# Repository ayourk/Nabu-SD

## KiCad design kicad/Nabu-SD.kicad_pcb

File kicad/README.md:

# SD Card Expansion & More!

Original design by Ken "The Codeman" Segler ([Youtube](https://www.youtube.com/@kensegler)) ([Github](https://github.com/TheCodeman))

## Description

The goal of this project is to make the PIC into a WD compatible FDD/HDD controller and function without any BIOS changes on the Nabu.  This means I'm going to have to learn how to write for the PIC in the project and what it takes to have it emulate a FDD/HDD controller as it uses the SD Card for storage.  The original project omitted the necessary flashable binary (or source) and links to the [SD Card](https://www.aliexpress.us/item/2251832622247273.html) and Serial Card breakout boards.

* A PDF version of the schematic can be found [here](Nabu-SD.pdf).
* Build of Materals (aka BOM) can be found [here](bom/ibom.html).

### PCB Layout

Some changes from the original by Ken "The Codeman" Segler:
* CR2032 battery - This is more common in PCs than the CR1220.
* The project was completely rebuilt in KiCAD 6.0.11.
* There are currently no Vias used on the main board with the 40-pin PDIP version of the PIC.
* I've focused on using more SMD parts where possible (except for the PIC) to make it easier to mass produce via a Fab House (e.g. [JLCPCB](https://www.jlcpcb.com/)).
* Corrected a few issues with the design with assistance from [@Stefanie80](https://github.com/Stefanie80).
* Created the SD Card and Serial Card breakouts and included them in schematic.  I am using UJ2-MIBH-4-SMT-TR because of the 3mm stick-out from the board.
* For the 2 Card breakouts, a lot of focus has been put into the amount of stick out of both the SD Card holder and the MicroUSB port so that a 3D Printed back plate can be used and still make it easy to remove a SD card or a MicroUSB cable.
* Created a 3D Model (.step) for the Nabu back plate for rear access to (1 or both) breakouts.  2x M2x20 screws and nuts will be included with preprinted model.

## TODO:

* Write the PIC code with [MPLab X IDE](https://www.microchip.com/en-us/tools-resources/develop/mplab-x-ide)
* Package everything up for [Arcade Shopper](https://www.arcadeshopper.com/) ([Github](https://github.com/arcadeshopper)) to sell.

Planned SD Card file naming scheme:  AHD12345.678
* A - Drive letter
* F or H - Floppy or HDD
* D or I - Usually "D", but use "I" for things like flux images.<br />
The rest will be some sort of amalgamation of Cylinders, Heads, Sectors.  This planned naming convention is subject to change depending on suggestions.

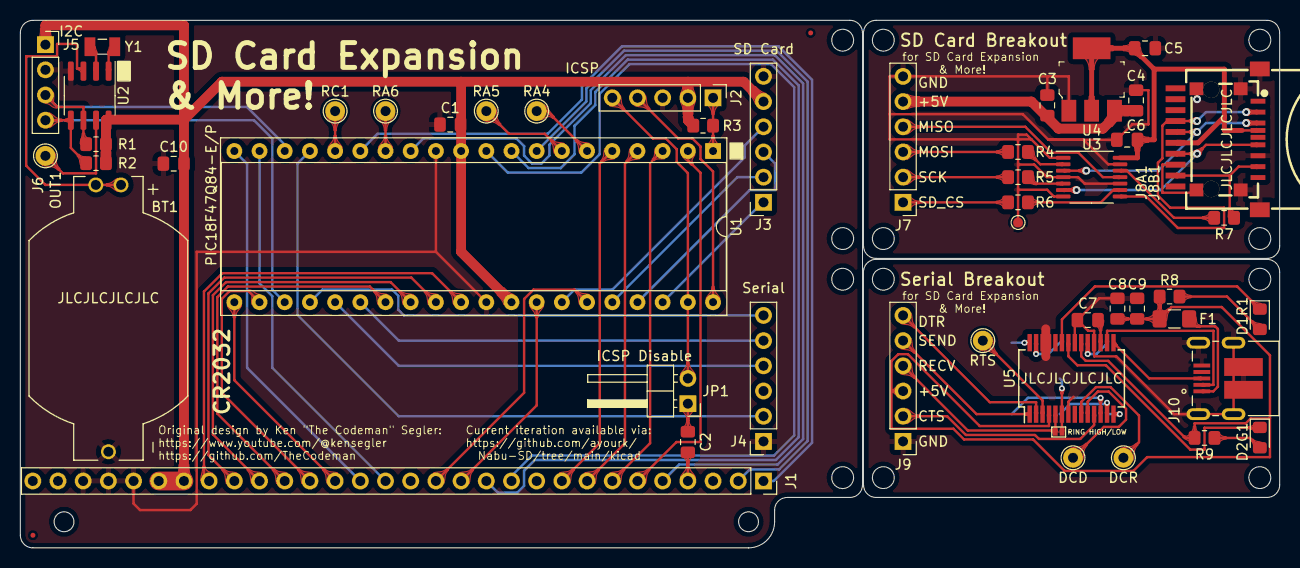
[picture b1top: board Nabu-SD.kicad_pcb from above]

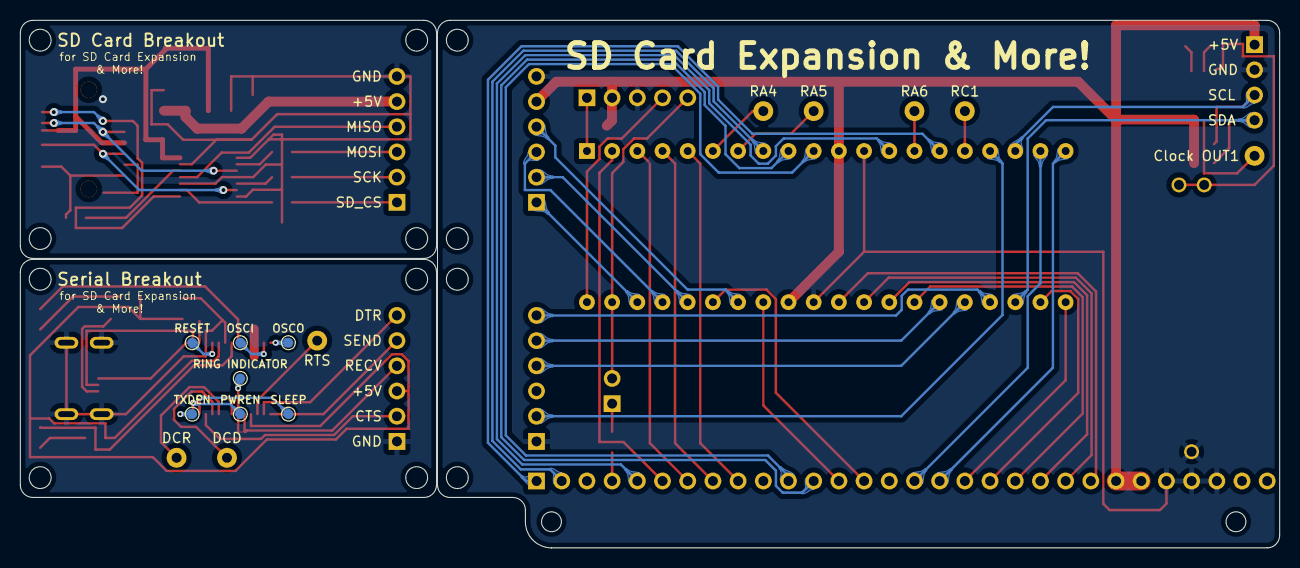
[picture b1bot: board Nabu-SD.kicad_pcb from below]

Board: 2 copper layers, 127.0 x 53.2 mm, 60 parts (7 on the bottom side), 71 nets.

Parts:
BT1: BU2032-1-HD-G; BAT_BU2032-1
C1, C4, C6, C7, C9: 0.1uF; C_0805_2012Metric_Pad1.18x1.45mm_HandSolder
C2: 1uF; C_0805_2012Metric_Pad1.18x1.45mm_HandSolder
C3, C5, C8, C10: 10uF; C_0805_2012Metric_Pad1.18x1.45mm_HandSolder
D1R1: TX_RED; LED_0805_2012Metric_Pad1.15x1.40mm_HandSolder
D2G1: RX_GREEN; LED_0805_2012Metric_Pad1.15x1.40mm_HandSolder
DCD: TestPoint_THTPad_D2.0mm_Drill1.0mm
DCR: TestPoint_THTPad_D2.0mm_Drill1.0mm
F1: MF-NSHT010KX-2; Fuse_1206_3216Metric_Pad1.42x1.75mm_HandSolder
J1: Nabu Expansion Slot; PinSocket_1x30_P2.54mm_Vertical
J2: ICSP; PinHeader_1x05_P2.54mm_Vertical
J3: SD Card; PinSocket_1x06_P2.54mm_Vertical
J4: Serial; PinSocket_1x06_P2.54mm_Vertical
J5: I2C; PinSocket_1x04_P2.54mm_Vertical
J6: OUT1; TestPoint_THTPad_D2.0mm_Drill1.0mm
J7: SD Card; PinHeader_1x06_P2.54mm_Vertical
J8A1: XKTF-005; TF-SMD_XKTF-005
J8B1: XKTF-0803-0; TF-SMD_XKTF-0803-0
J9: Serial; PinHeader_1x06_P2.54mm_Vertical
J10: USB_B_Micro; CUI_UJ2-MIBH-4-SMT
JP1: ICSP Disable; PinHeader_1x02_P2.54mm_Horizontal
OSCI: TestPoint_Pad_D1.0mm
OSCO: TestPoint_Pad_D1.0mm
PWREN: TestPoint_Pad_D1.0mm
R1, R2, R3: 10K; R_0805_2012Metric_Pad1.20x1.40mm_HandSolder
R4, R5, R6, R7: 3.3K; R_0805_2012Metric_Pad1.20x1.40mm_HandSolder
R8, R9: 330; R_0805_2012Metric_Pad1.20x1.40mm_HandSolder
RA4, RA5, RA6: TestPoint_THTPad_D2.0mm_Drill1.0mm
RC1: TestPoint_THTPad_D2.0mm_Drill1.0mm
REF1, REF2: Fiducial_0.5mm_Mask1mm
REF3, REF4: MountingHole_2mm
RESET: TestPoint_Pad_D1.0mm
RING HIGH/LOW: SolderJumper-2_P0.65mm_Bridged2Bar_Pad0.5x0.75mm; SolderJumper-2_P0.65mm_Bridged1Bar_Pad0.5x0.75mm
RING INDICATOR: TestPoint_Pad_D1.0mm
RTS: TestPoint_THTPad_D2.0mm_Drill1.0mm
SLEEP: TestPoint_Pad_D1.0mm
TXDEN: TestPoint_Pad_D1.0mm
U1: PIC18F47Q84-E/P; DIP-40_W15.24mm_Socket
U2: DS1307N+; SOIC-8_3.9x4.9mm_P1.27mm
U3: 74LVC125; TSSOP-14_4.4x5mm_P0.65mm
U4: LM1117-3.3; SOT-223
U5: FT232RL; SSOP-28_5.3x10.2mm_P0.65mm
Y1: 32KHz; XTAL_ECS-.327-12.5-34B

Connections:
+3V3: C5.1, C6.2, J8A1.4 (VDD), J8B1.4 (VDD), U3.14 (VCC), U4.2 (VO), U4.4 (VO)
+5V: C1.2, C3.1, C4.1, C10.1, J1.24, J1.25, J2.2, J3.5, J5.1, J7.5, R1.2, R2.2, R3.1, U1.11 (VDD), U1.32 (VDD), U2.8 (VCC), U4.3 (VI)
+5VD: C8.1, C9.1, F1.1, J4.3, J9.3, R8.1, R9.1, U5.4 (VCCIO), U5.20 (VCC)
/A0: J1.6, U1.2 (RA0)
/A1: J1.7, U1.3 (RA1)
/A2: J1.8, U1.4 (RA2)
/A3: J1.9, U1.5 (RA3)
/AUDIO: C2.1, J1.4
/D0: J1.16, U1.19 (RD0)
/D1: J1.17, U1.20 (RD1)
/D2: J1.18, U1.21 (RD2)
/D3: J1.19, U1.22 (RD3)
/D4: J1.20, U1.27 (RD4)
/D5: J1.21, U1.28 (RD5)
/D6: J1.22, U1.29 (RD6)
/D7: J1.23, U1.30 (RD7)
/MISO: J3.4, J7.4, U1.34 (RB1), U3.11
/MOSI: J3.3, J7.3, R4.1, U1.37 (RB4)
/MicroSD_Breakout/SD_CLK: J8A1.5 (CLK), J8B1.5 (CLK), U3.6
/MicroSD_Breakout/SD_MISO: J8A1.7 (DAT0), J8B1.7 (DAT0), R7.2
/MicroSD_Breakout/SD_MOSI: J8A1.3 (CMD), J8B1.3 (CMD), U3.3
/MicroSD_Breakout/SD_SSEL: J8A1.2 (CD/DAT3), J8B1.2 (CD/DAT3), U3.8
/RA4: RA4.1, U1.6 (RA4)
/RA5: RA5.1, U1.7 (RA5)
/RA6: RA6.1, U1.14 (RA6)
/RB6: J2.5, JP1.2 (B), U1.39 (RB6/ICSPCLK)
/RB7: J2.4, U1.40 (RB7/ICSPDAT)
/RC1: RC1.1, U1.16 (RC1)
/RC2: J4.2, J9.2, U1.17 (RC2), U5.11 (CTS)
/RC5: J4.6, J9.6, U1.24 (RC5), U5.2 (DTR)
/RX1: J4.4, J9.4, RING HIGH/LOW.1, RING HIGH/LOW.2, RING INDICATOR.1, U1.25 (RC6), U5.5 (RXD), U5.6 (RI)
/SCL: J5.3, R1.1, U1.18 (RC3), U2.6 (SCL)
/SDA: J5.4, R2.1, U1.23 (RC4), U2.5 (SDA)
/SD_CS: J3.1, J7.1, R6.1, U1.38 (RB5)
/SPISCK: J3.2, J7.2, R5.1, U1.36 (RB3)
/Serial_Breakout/3V3OUT: C7.2, U5.17 (3V3OUT)
/Serial_Breakout/DCD: DCD.1, U5.10 (DCD)
/Serial_Breakout/DCR: DCR.1, U5.9 (DCR)
/Serial_Breakout/OSCI: OSCI.1, U5.27 (OSCI)
/Serial_Breakout/OSCO: OSCO.1, U5.28 (OSCO)
/Serial_Breakout/PWREN: PWREN.1, U5.13 (CBUS2)
/Serial_Breakout/RTS: RTS.1, U5.3 (RTS)
/Serial_Breakout/RXLED_GRN: D2G1.1 (K), U5.22 (CBUS1)
/Serial_Breakout/SLEEP: SLEEP.1, U5.12 (CBUS4)
/Serial_Breakout/TXDEN: TXDEN.1, U5.14 (CBUS3)
/Serial_Breakout/TXLED_RED: D1R1.1 (K), U5.23 (CBUS0)
/Serial_Breakout/USBDATA1: J10.2 (DATA-), U5.16 (USBD-)
/Serial_Breakout/USBDATA+: J10.3 (DATA+), U5.15 (USBD+)
/Serial_Breakout/~RESET: RESET.1, U5.19 (~RESET)
/TX1: J4.5, J9.5, U1.26 (RC7), U5.1 (TXD)
/VBAT: BT1.S1+, BT1.S2+, U2.3 (VBAT)
//CS: J1.5, U1.13 (RA7)
//INT: J1.1, U1.15 (RC0)
//IORQ: J1.13, U1.33 (RB0)
//M1: J1.2, U1.8 (RE0)
//RD: J1.12, U1.9 (RE1)
//WAIT: J1.14, U1.35 (RB2)
//WR: J1.11, U1.10 (RE2)
/~MCLR: J2.1, R3.2, U1.1 (MCLR/VPP/RE3)
GND: BT1.-, C1.1, C3.2, C4.2, C5.2, C6.1, C7.1, C8.2, C9.2, C10.2, J1.26, J1.27, J1.28, J2.3, J3.6, J4.1, J5.2, J7.6, J8A1.6 (VSS), J8A1.11 (GND), J8A1.12 (GND), J8B1.6 (VSS), J8B1.10 (SHELL), J8B1.11 (SHELL), J8B1.12 (SHELL), J8B1.13 (SHELL), J9.1, J10.5 (GND), J10.SH1 (SHIELD), J10.SH2 (SHIELD), J10.SH3 (SHIELD), J10.SH4 (SHIELD), J10.SH5 (SHIELD), J10.SH6 (SHIELD), U1.12 (VSS), U1.31 (VSS), U2.4 (GND), U3.1, U3.4, U3.7 (GND), U3.10, U3.13, U4.1 (GND), U5.7 (GND), U5.18 (GND), U5.21 (GND), U5.25 (AGND), U5.26 (TEST)
unnamed: C2.2, JP1.1 (A)
unnamed: D1R1.2 (A), R8.2
unnamed: D2G1.2 (A), R9.2
unnamed: F1.2, J10.1 (VBUS)
unnamed: J6.1, U2.7 (SQW/OUT)
unnamed: R4.2, U3.2
unnamed: R5.2, U3.5
unnamed: R6.2, U3.9
unnamed: R7.1, U3.12
unnamed: U2.1 (X1), Y1.2
unnamed: U2.2 (X2), Y1.1

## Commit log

2023-04-22 Converted from EasyEDA and optimized routing. Zero Vias used.
2023-04-22 Corrected 1 resistor value; Added a Solder Jumper to close AFTER flashing PIC. Reduced the size of the board. Moved to mostly SMD parts (where possible).
2023-04-22 This Project uses CR2032 vs CR1220; Added README; Updated silkscreen; Added missing KiCAD project file.
2023-04-22 Formatting fixes.
2023-04-23 Added link to SD Card module
2023-04-23 Update SD Card Module link
2023-04-23 Update credit links to people.
2023-04-28 Created the SD Card and Serial Card breakouts and included them in schematic. Prettied up all of the 3D Models and rendered them in the board view. Added all used external models, footprints, and sym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
2023-04-28 Fix a small formatting issue.
2023-04-28 Downsize main image for use when posting repo on all the Socials.
2023-04-30 Made the PCB render more fancy and cleaned up dependent STEP files.
2023-05-02 Updated LCSC part mappings. Updated LM1117-3.3 model and regenerated the PCB render.
2023-05-03 Shuffled around PIC pins around for I2C and Serial CTS signals to be more inline with the datasheet for this specific PIC.
2023-05-07 Update +5V and +3V3 voltage trace widths per @K3130440 and greghol.
2023-05-07 Added Teardrops.
2023-05-11 Added Vias and test points for Serial Breakout board.
2023-05-11 Fix Schematic Parity issue.
2023-05-24 Update fill zones for PCB manufacture.
2023-07-07 Rotate Green LED 180 degrees on Serial breakout.
2023-07-27 First draft of Backplate for breakout PCBs.
2023-07-31 Final? backplate mount for both breakout boards.
2023-07-31 3D Backplate Model complete
2024-01-04 Update README.md
    Adjustment to what is and is not included.
